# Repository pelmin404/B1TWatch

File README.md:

# B1TWatch
### A low power, Li-ion/LiPo battery powered binary watch with an exposed PCB, automatic brightness, and interactive settings based on a Seeed Studio XIAO MG24 Sense

## 🛠️ Size and design:
The board is 5 cm wide and 4.25 cm tall, with chamfered corners, and is meant to be press-fitted into a strap with a battery. For customization purposes it has an empty space on its bottom left corner reserved for graphics or extra components. By default the board has no silkscreen besides settings markings in "Silkscreen" font.

## ⚡ Power:
Because the board is using a Seeed Studio XIAO MG24 Sense, any battery that complies with [this guide](https://wiki.seeedstudio.com/xiao_mg24_getting_started/#battery-usage) can be connected to the JST connector present on the board.

**However the user needs to make sure that the positive and negative terminals on the female JST connector of the battery are in the right orientation by confirming that the side of the male JST connector on the board that will be connected to the positive wire has a trace connecting it to the XIAO. Otherwise permanent damage may be caused**

## 🎨 Customization:
The provided .ino file has lots of comments that explain what each part does and what values to change for customization. Along software, the PCB can be customized as well, mainly by using the reserved empty space. However if extra electronic components are added, the XIAO's current limits have to be accounted for.

## ⚙️ Manual:
In this manual, the rotary encoder will be referred to as a watch crown.
### Overview:
B1TWatch has 4 modes: Idle, Time, Configuration, and Calibration.
* Idle mode puts the XIAO into a power saving sleep mode and keeps its RTC active.
* Time mode shows time and opens access to Configuration and Calibration modes.
* Configuration mode lets you manage timers, alarms, and stopwatches, and change watch settings.
* Calibration mode lets you calibrate the watch manually or via Bluetooth connection to a smartphone, laptop, or a PC.

### Configuration Mode and Labels:
To access the Configuration mode, press the crown once. You will see a lit up bar indicating the chosen setting menu.

Every configuration setting is labeled with its initial from left to right in this order:
* **T**imer
* **A**larm
* **S**topwatch
* **V**olume/**F**requency
* **B**rightness
* **F**ormat

To open any setting menu, rotate the crown either way until the lit up LED bar is in line with the corresponding setting label, and press the crown once.

To exit out of any setting menu at any moment and discard all changes, press and hold the crown for 1 second by default.

### Timer:
To set a timer, enter the Configuration mode and select the Timer menu, then press the crown once. The bottom row of LEDs will light up indicating that the current selected time option is seconds. Rotate the crown either way to adjust desired time in the selected row. Press the crown once to confirm changes and select the row above, or press 2 times to select the row below. Once the desired time is set, select the hour row and press the crown once to start the timer. When the timer is active, its countdown will be displayed by default in Time mode until it is triggered or canceled. Rotate the crown in either direction to switch between viewing the current time and the timer countdown.

To change the active timer length, open the Timer menu and follow timer setup steps and set the new desired time, the active timer will keep counting down to the new time without restarting. To cancel the active timer, change its length to 0 seconds.

Note: If the new timer length is equal to or smaller than the time which it has already been active for, it will be triggered immediately.

### Alarm:
The Alarm menu has multiple steps. To revert any step past the 1st one and return to the previous step, double press the crown on the lowest selected row (if applicable).

#### Step 1:
Enter the Configuration mode and open the Alarm menu. The first step of alarm setup will be selected in this step select one out of 64 possible alarms using the crown and the bottom row of the matrix, counting in binary. If a selected alarm exists, the leftmost LED on the top row will light up. Press the crown to continue.

#### Step 2:
The bottom row of LEDs will light up indicating that the current selected time option is seconds. Rotate the crown either way to adjust desired time in the selected row. Press the crown once to confirm changes and select the row above, or press 2 times to select the row below. Once the desired time is set, select the hour row and press the crown once to continue.

#### Step 3:
Add the active weekdays for the alarm by rotating the crown and counting in binary to the corresponding weekday number, with Monday being 1 and Sunday being 7. Press the crown once to add an active day. When selecting an already active weekday, the leftmost LED on the top row will light up. Press the crown once to remove the weekday. To start will all weekdays active and subtract them instead, select weekday 0 and press the crown once. All LEDs will light up and counting will be indicated by LEDs that are off. Select weekday 0 again and press the crown once to switch back to the addition mode. Switching between these 2 modes discards changes on this step.

To apply the alarm, rotate the crown past weekday 7, an indication bar on the middle row will be displayed. Press the crown once to confirm all changes. If the bar flashes and nothing else happens, it means no weekdays are active. Otherwise an animation will be played and B1TWatch will switch to Time mode, indicating a successful operation.

To delete an alarm, select an alarm following instructions from [step 1](#step-1), set its time to 0 seconds and press the crown once. Setting selection menu will then be opened.

### Stopwatch:
To start a stopwatch, enter the Configuration mode and select the Stopwatch menu, then press the crown once. First, set a desired countdown after which the stopwatch will start. The bottom row of LEDs will light up indicating that the current selected time option is seconds. Rotate the crown either way to adjust desired countdown time in the selected row. Press the crown once to confirm changes and select the row above, or press 2 times to select the row below. Once the desired countdown time is set, select the hour row and press the crown once to start the countdown. To pause or resume the stopwatch, press the crown once. To reset the stopwatch and go back to countdown selection, double press the crown while the stopwatch is paused.

### Volume/Frequency:
To change volume and/or frequency of the piezo buzzer, enter the Configuration mode and select the Volume/Frequency menu, then press the crown once. Rotate the crown either way to adjust desired volume in increments of 10%. Once the desired time is set, select the hour row and press the crown once to continue. Then rotate the crown either way to adjust desired frequency in hHz, and press the crown once to apply changes, or twice to return to volume setting.

### Brightness:
To change the minimum and maximum brightness, enter the Configuration mode and select the Brightness menu, then press the crown once. Rotate the crown either way to adjust desired minimum brightness in increments of 10% and press the crown once to continue. Then rotate the crown either way to adjust desired maximum brightness in increments of 10%, and press the crown once to apply changes, or twice to return to minimum brightness setting.

### Format:
To change the time format, enter the Configuration mode and select the Format menu, then press the crown once. The middle row will then show a binary 12 or 24, indicating the corresponding current time format. Rotate the crown either way to change it, and press it once to confirm changes.

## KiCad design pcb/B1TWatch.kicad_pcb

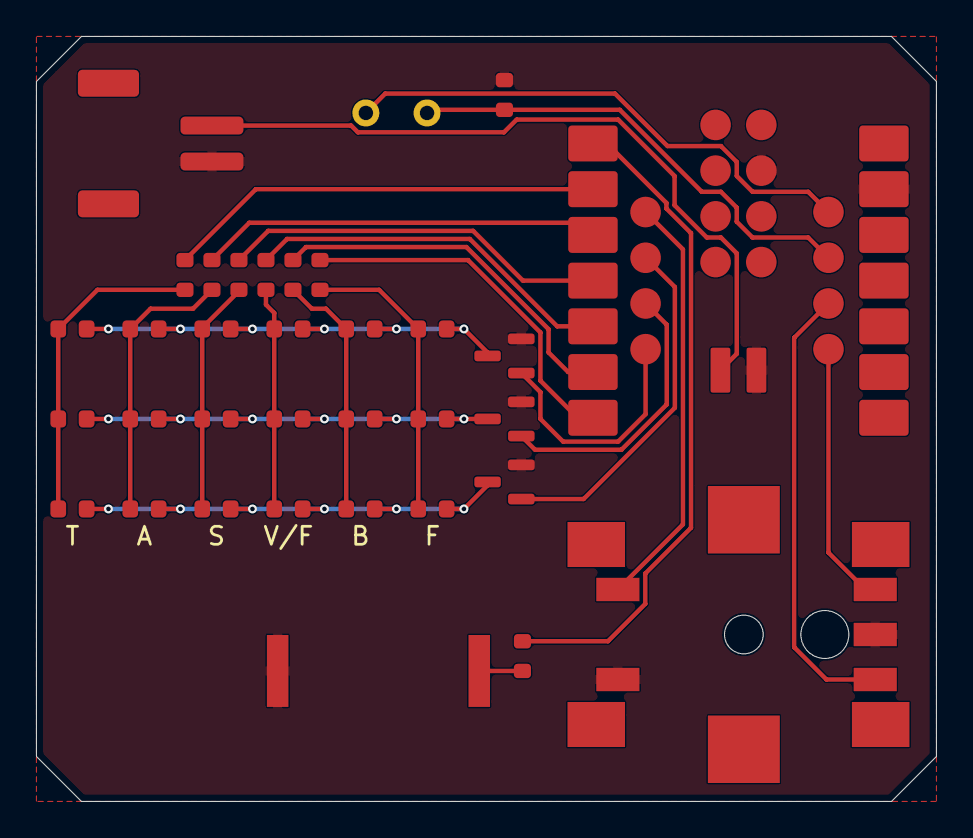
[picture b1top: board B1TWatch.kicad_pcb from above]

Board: 2 copper layers, 50.0 x 42.5 mm, 34 parts (0 on the bottom side), 27 nets.

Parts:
BZ1: Buzzer; Buzzer_Murata_PKLCS1212E
D1, D2, D3, D4, D5, D6, D7, D8, D9, D10, D11, D12, D13, D14, D15, D16, D17, D18: LED; LED_0603_1608Metric
J1: Conn_01x02_Pin; JST_PH_S2B-PH-SM4-TB_1x02-1MP_P2.00mm_Horizontal
Q1, Q2, Q3: Q_NMOS_GSD; SOT-23
R1, R2, R3, R4, R5, R6: 56; R_0603_1608Metric
R7: 10k; R_0603_1608Metric
R8: LDR07; R_LDR_5.1x4.3mm_P3.4mm_Vertical
R9: 1k; R_0603_1608Metric
SW1: RotaryEncoder_Switch; PEC11S9213KS0015
U1: XIAO-MG24-SMD

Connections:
GND: BZ1.2 (-), J1.2, Q1.2 (S), Q2.2 (S), Q3.2 (S), R7.2, SW1.C, SW1.S1, U1.13 (GND), U1.29 (GND), U1.32 (GND)
unnamed: BZ1.1 (+), R9.1
unnamed: D1.2 (A), D7.2 (A), D13.2 (A), R6.1
unnamed: D1.1 (K), D2.1 (K), D3.1 (K), D4.1 (K), D5.1 (K), D6.1 (K), Q3.3 (D)
unnamed: D4.2 (A), D10.2 (A), D16.2 (A), R3.1
unnamed: D7.1 (K), D8.1 (K), D9.1 (K), D10.1 (K), D11.1 (K), D12.1 (K), Q2.3 (D)
unnamed: D5.2 (A), D11.2 (A), D17.2 (A), R2.1
unnamed: D6.2 (A), D12.2 (A), D18.2 (A), R1.1
unnamed: D13.1 (K), D14.1 (K), D15.1 (K), D16.1 (K), D17.1 (K), D18.1 (K), Q1.3 (D)
unnamed: D2.2 (A), D8.2 (A), D14.2 (A), R5.1
unnamed: D3.2 (A), D9.2 (A), D15.2 (A), R4.1
unnamed: J1.1, U1.31 (BAT)
unnamed: Q1.1 (G), U1.19 (D15)
unnamed: Q2.1 (G), U1.20 (D16)
unnamed: Q3.1 (G), U1.21 (D17)
unnamed: R9.2, U1.1 (D0)
unnamed: R1.2, U1.2 (D1)
unnamed: R2.2, U1.3 (D2)
unnamed: R3.2, U1.4 (D3)
unnamed: R4.2, U1.5 (D4)
unnamed: R5.2, U1.6 (D5)
unnamed: R6.2, U1.7 (D6)
unnamed: R8.1, U1.15 (D11)
unnamed: R7.1, R8.2, U1.16 (D12)
unnamed: SW1.A, U1.17 (D13)
unnamed: SW1.B, U1.18 (D14)
unnamed: SW1.S2, U1.22 (D18)
